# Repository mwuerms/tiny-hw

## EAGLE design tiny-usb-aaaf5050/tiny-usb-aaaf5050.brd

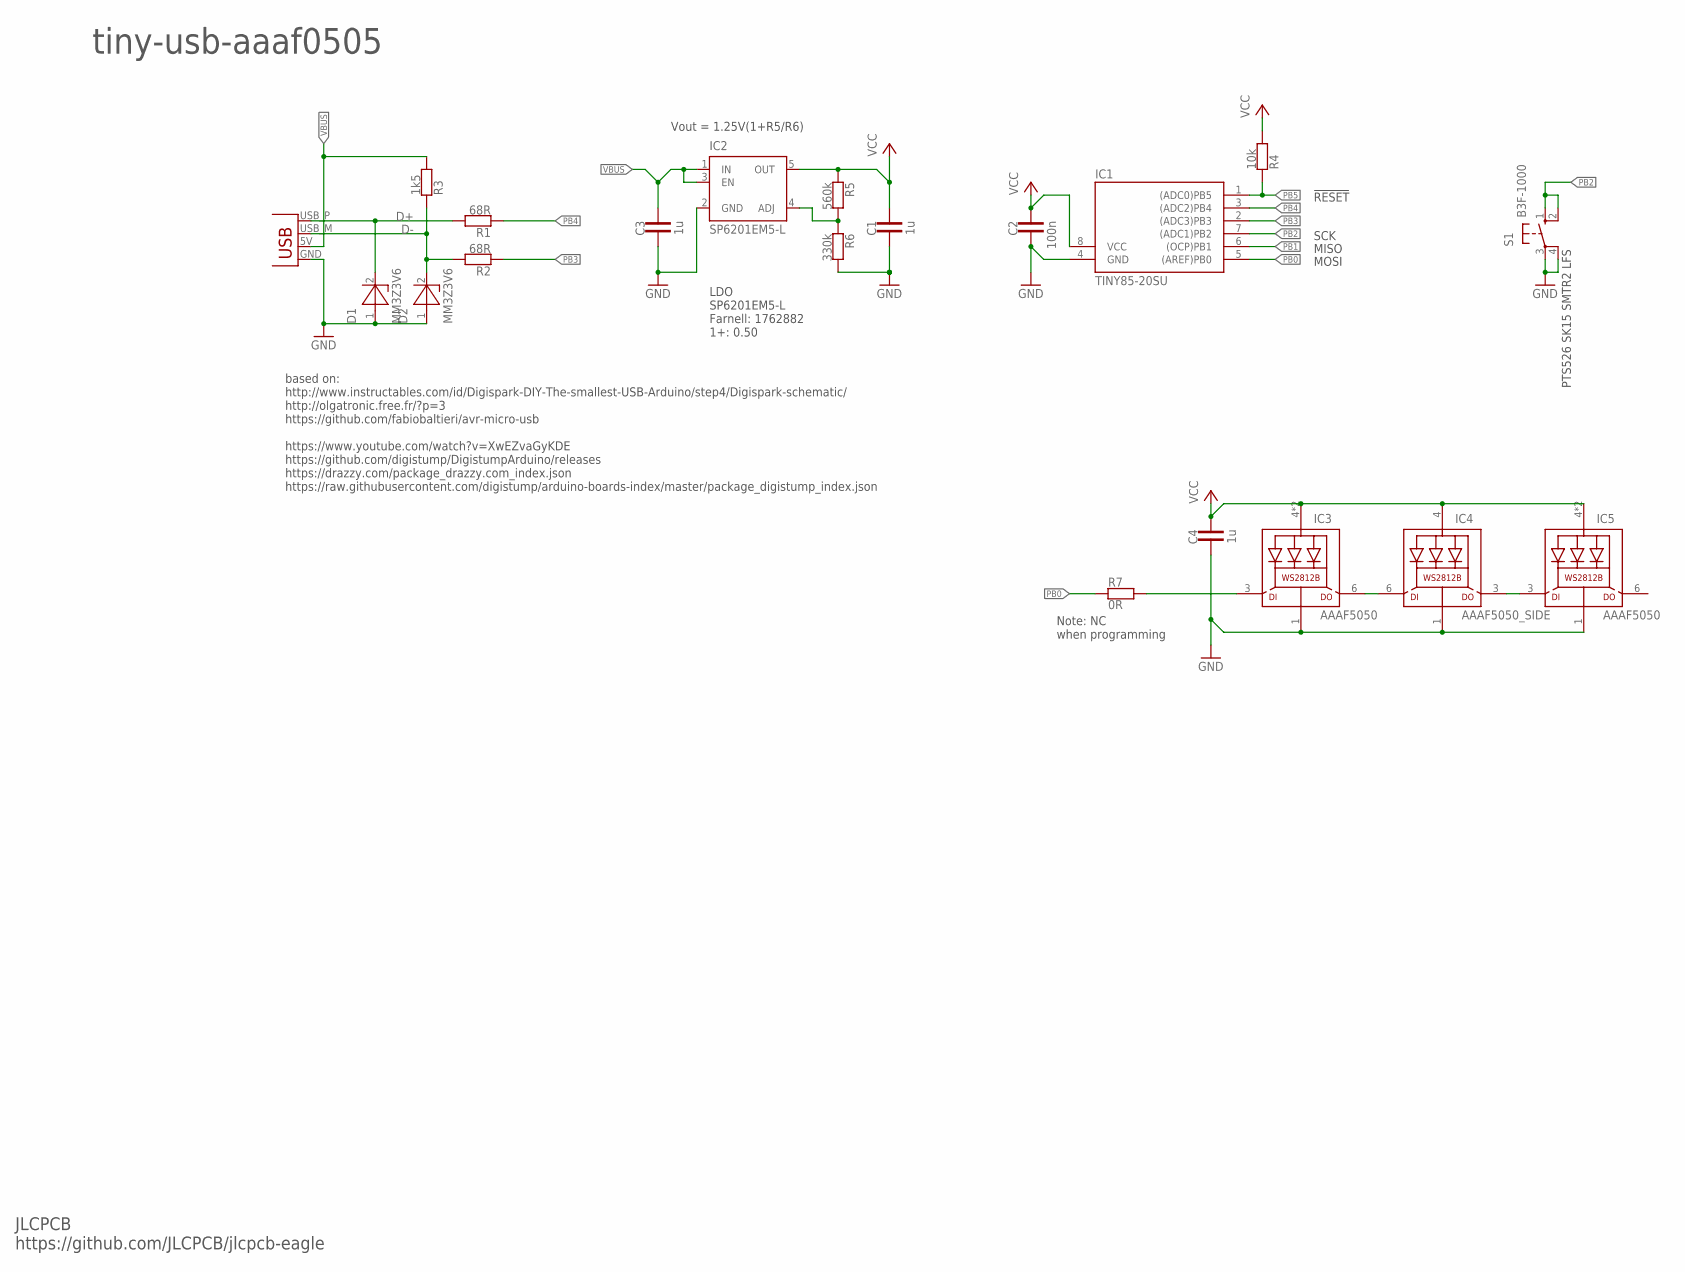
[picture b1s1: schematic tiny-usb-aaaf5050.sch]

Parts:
C1, C3: 1u; 0603MIL
C2: 100n; 0603MIL
C4: 1u; 0805MIL
D1, D2: MM3Z3V6; SOD-923F
IC1: TINY85-20SU; SOIC8
IC2: SP6201EM5-L; SOT23-5
IC3, IC5: AAAF5050
IC4: AAAF5050_SIDE
R1, R2: 68R; 0603MIL
R3: 1k5; 0603MIL
R4: 10k; 0603MIL
R5: 560k; 0603MIL
R6: 330k; 0603MIL
R7: 0R; 0603MIL
S1: B3F-1000; B3F-10SMD
X1: USBPCB; USB-A-PCB

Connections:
D+: D1.2 (K), R1.2, X1.USB_P (D+)
D-: D2.2 (K), R2.2, R3.1, X1.USB_M (D-)
DIN1: IC3.3 (DI), R7.2
DIN2: IC3.6 (DO), IC4.6 (DI)
DIN3: IC4.3 (DO), IC5.3 (DI)
GND: C1.2, C2.2, C3.2, C4.2, D1.1 (A), D2.1 (A), IC1.4 (GND), IC2.2 (GND), IC3.1 (GND), IC4.1 (GND), IC5.1 (GND), R6.2, S1.3, S1.4 (P1), X1.GND
unnamed: IC2.4 (ADJ), R5.2, R6.1
PB0: IC1.5 ((AREF)PB0), R7.1
PB1: IC1.6 ((OCP)PB1)
PB2: IC1.7 ((ADC1)PB2), S1.1 (S), S1.2 (S1)
PB3: IC1.2 ((ADC3)PB3), R2.1
PB4: IC1.3 ((ADC2)PB4), R1.1
PB5: IC1.1 ((ADC0)PB5), R4.1
VBUS: C3.1, IC2.1 (IN), IC2.3 (EN), R3.2, X1.5V (VBUS)
VCC: C1.1, C2.1, C4.1, IC1.8 (VCC), IC2.5 (OUT), IC3.4 (VDD), IC3.5 (VDD), IC4.4 (VDD), IC5.4 (VDD), IC5.5 (VDD), R4.2, R5.1

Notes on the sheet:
based on: http://www.instructables.com/id/Digispark-DIY-The-smallest-USB-Arduino/step4/Digispark-schematic/ http://olgatronic.free.fr/?p=3 https://github.com/fabiobaltieri/avr-micro-usb https://www.youtube.com/watch?v=XwEZvaGyKDE https://github.com/digistump/DigistumpArduino/releases https://drazzy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
LDO SP6201EM5-L Farnell: 1762882 1+: 0.50
Vout = 1.25V(1+R5/R6)
tiny-usb-aaaf0505
JLCPCB https://github.com/JLCPCB/jlcpcb-eagle
PTS526 SK15 SMTR2 LFS
!RESET!
MOSI
MISO
SCK
Note: NC when programming

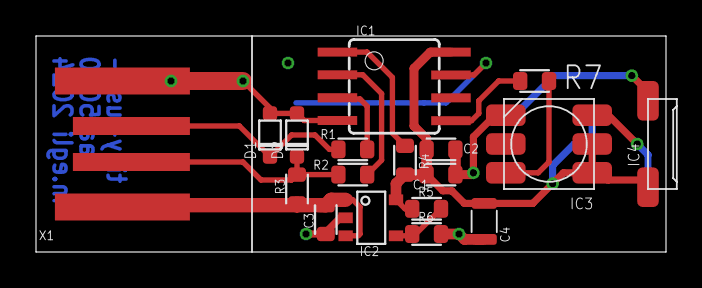
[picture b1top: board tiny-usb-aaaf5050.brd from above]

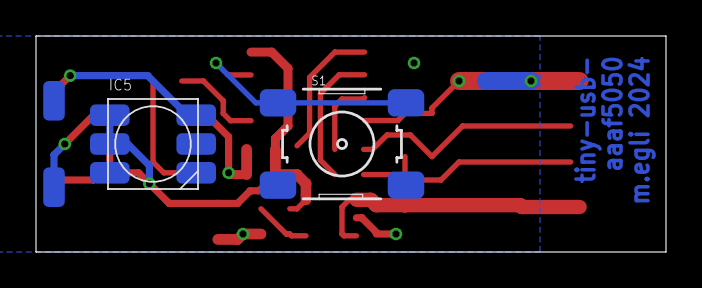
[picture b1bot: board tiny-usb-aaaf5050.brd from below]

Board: 2 copper layers, 35.0 x 12.0 mm, 20 parts (2 on the bottom side), 14 nets.

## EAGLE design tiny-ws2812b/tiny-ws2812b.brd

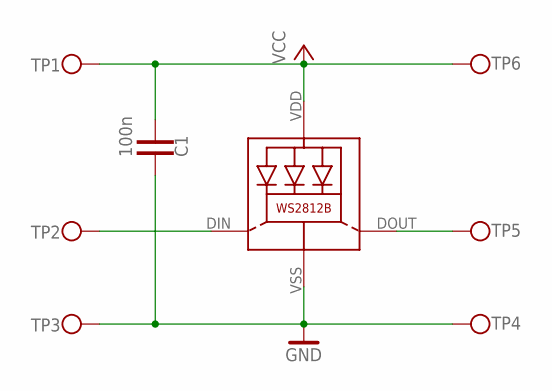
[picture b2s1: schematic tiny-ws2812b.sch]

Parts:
C1: 100n; 0603MIL
LED1: WS2812B
TP1, TP2, TP3, TP4, TP5, TP6: TP_Q2X1MM; PAD_Q2X1MM

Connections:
GND: C1.1, LED1.VSS (GND), TP3.1, TP4.1
unnamed: LED1.DOUT (DO), TP5.1
unnamed: LED1.DIN (DI), TP2.1
VCC: C1.2, LED1.VDD, TP1.1, TP6.1

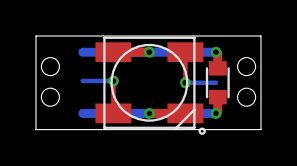
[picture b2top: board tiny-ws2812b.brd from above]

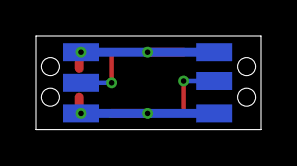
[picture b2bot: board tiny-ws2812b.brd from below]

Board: 2 copper layers, 12.5 x 5.2 mm, 8 parts (6 on the bottom side), 4 nets.

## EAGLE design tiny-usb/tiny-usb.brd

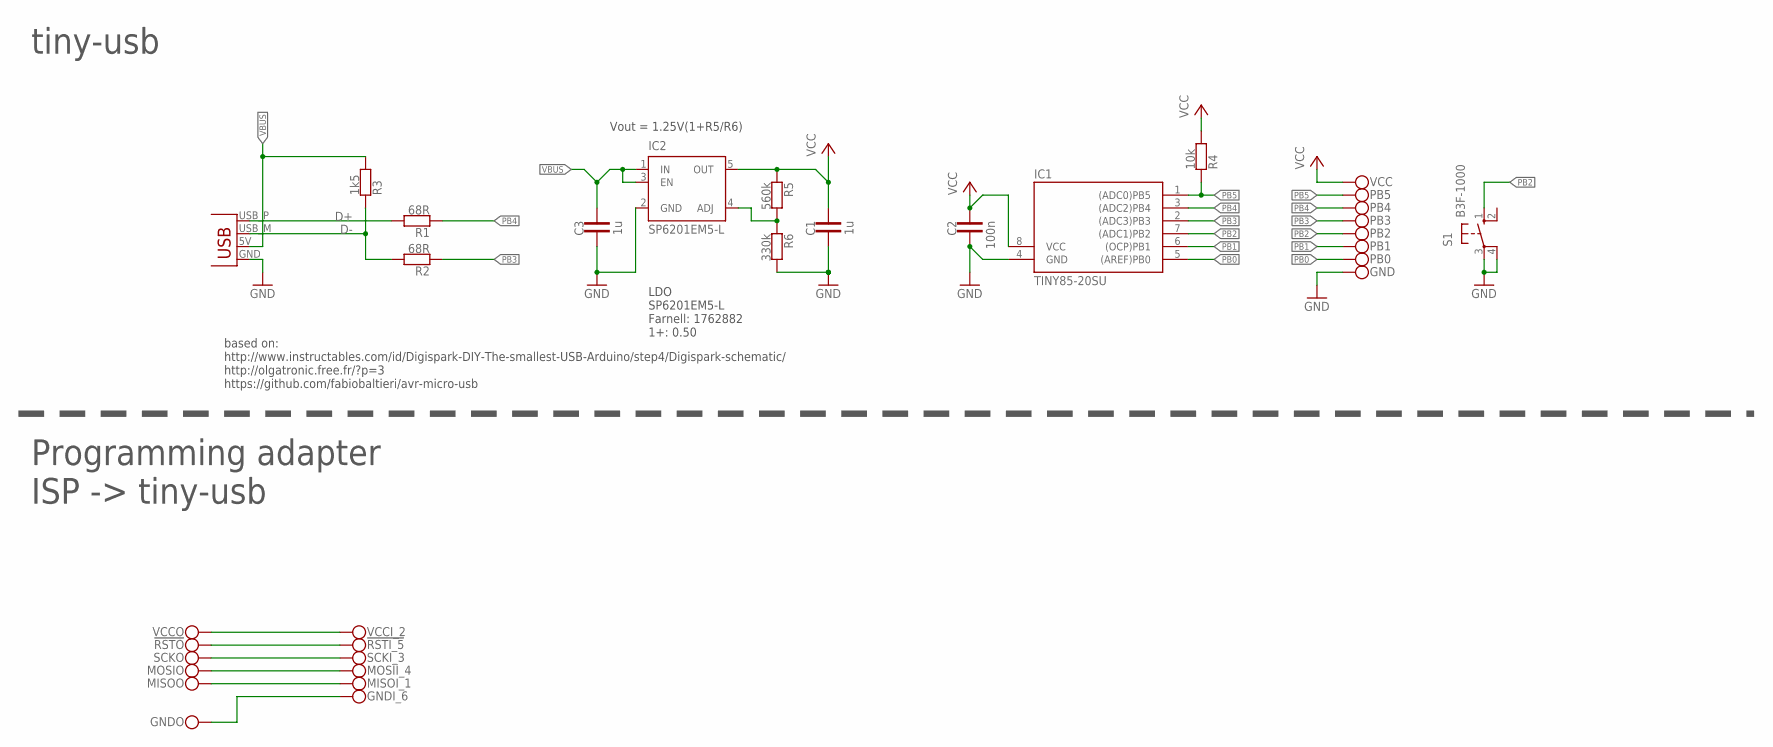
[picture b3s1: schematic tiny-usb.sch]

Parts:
!RSTI_5: TP_Q3X1.5MM; PAD_Q1.5X3MM
!RSTO: TP_Q3X1.5MM; PAD_Q1.5X3MM
C1, C3: 1u; 0603MIL
C2: 100n; 0603MIL
GND: TP_Q3X1.5MM; PAD_Q1.5X3MM
GNDI_6: TP_Q3X1.5MM; PAD_Q1.5X3MM
GNDO: TP_Q3X1.5MM; PAD_Q1.5X3MM
IC1: TINY85-20SU; SOIC8
IC2: SP6201EM5-L; SOT23-5
MISOI_1: TP_Q3X1.5MM; PAD_Q1.5X3MM
MISOO: TP_Q3X1.5MM; PAD_Q1.5X3MM
MOSII_4: TP_Q3X1.5MM; PAD_Q1.5X3MM
MOSIO: TP_Q3X1.5MM; PAD_Q1.5X3MM
PB0, PB1, PB2, PB3, PB4, PB5: TP_Q3X1.5MM; PAD_Q1.5X3MM
R1, R2: 68R; 0603MIL
R3: 1k5; 0603MIL
R4: 10k; 0603MIL
R5: 560k; 0603MIL
R6: 330k; 0603MIL
S1: B3F-1000; B3F-10SMD
SCKI_3: TP_Q3X1.5MM; PAD_Q1.5X3MM
SCKO: TP_Q3X1.5MM; PAD_Q1.5X3MM
VCC: TP_Q3X1.5MM; PAD_Q1.5X3MM
VCCI_2: TP_Q3X1.5MM; PAD_Q1.5X3MM
VCCO: TP_Q3X1.5MM; PAD_Q1.5X3MM
X1: USBPCB; USB-A-PCB

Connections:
!ISP_RST: !RSTI_5.1, !RSTO.1
D+: R1.2, X1.USB_P (D+)
D-: R2.2, R3.1, X1.USB_M (D-)
GND: C1.2, C2.2, C3.2, GND.1, IC1.4 (GND), IC2.2 (GND), R6.2, S1.3, S1.4 (P1), X1.GND
ISP_GND: GNDI_6.1, GNDO.1
ISP_MISO: MISOI_1.1, MISOO.1
ISP_MOSI: MOSII_4.1, MOSIO.1
ISP_SCK: SCKI_3.1, SCKO.1
ISP_VCC: VCCI_2.1, VCCO.1
unnamed: IC2.4 (ADJ), R5.2, R6.1
PB0: IC1.5 ((AREF)PB0), PB0.1
PB1: IC1.6 ((OCP)PB1), PB1.1
PB2: IC1.7 ((ADC1)PB2), PB2.1, S1.1 (S)
PB3: IC1.2 ((ADC3)PB3), PB3.1, R2.1
PB4: IC1.3 ((ADC2)PB4), PB4.1, R1.1
PB5: IC1.1 ((ADC0)PB5), PB5.1, R4.1
VBUS: C3.1, IC2.1 (IN), IC2.3 (EN), R3.2, X1.5V (VBUS)
VCC: C1.1, C2.1, IC1.8 (VCC), IC2.5 (OUT), R4.2, R5.1, VCC.1

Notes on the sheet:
based on: http://www.instructables.com/id/Digispark-DIY-The-smallest-USB-Arduino/step4/Digispark-schematic/ http://olgatronic.free.fr/?p=3 https://github.com/fabiobaltieri/avr-micro-usb
LDO SP6201EM5-L Farnell: 1762882 1+: 0.50
Vout = 1.25V(1+R5/R6)
tiny-usb
Programming adapter ISP -> tiny-usb

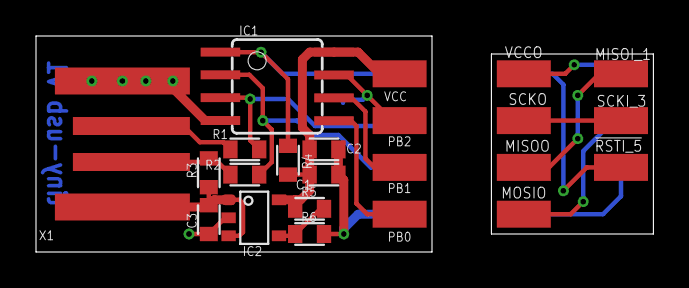
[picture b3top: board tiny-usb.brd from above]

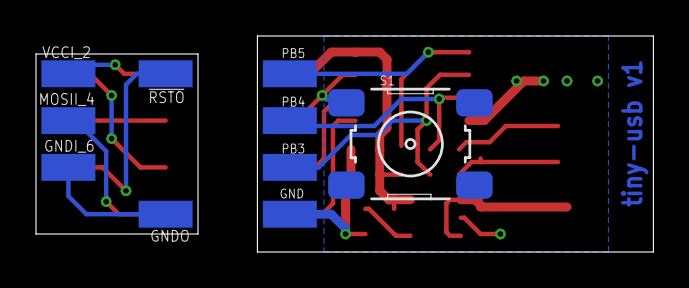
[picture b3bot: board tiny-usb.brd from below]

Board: 2 copper layers, 34.3 x 12.0 mm, 33 parts (10 on the bottom side), 18 nets.

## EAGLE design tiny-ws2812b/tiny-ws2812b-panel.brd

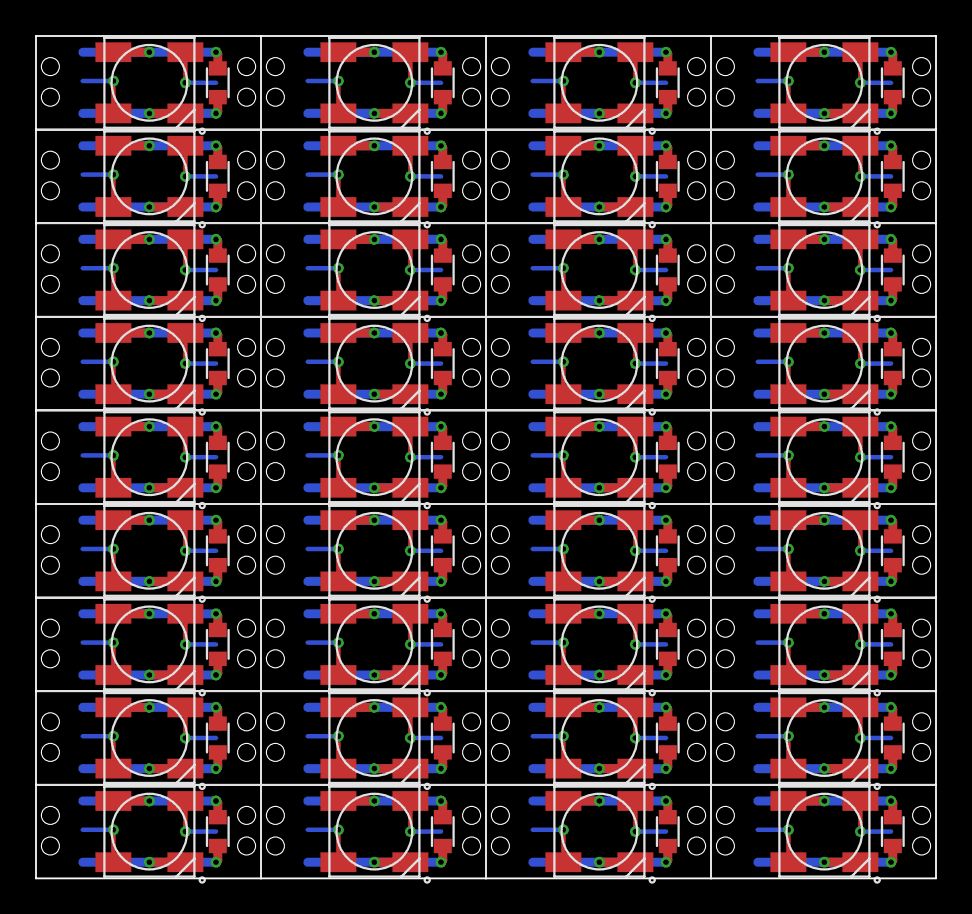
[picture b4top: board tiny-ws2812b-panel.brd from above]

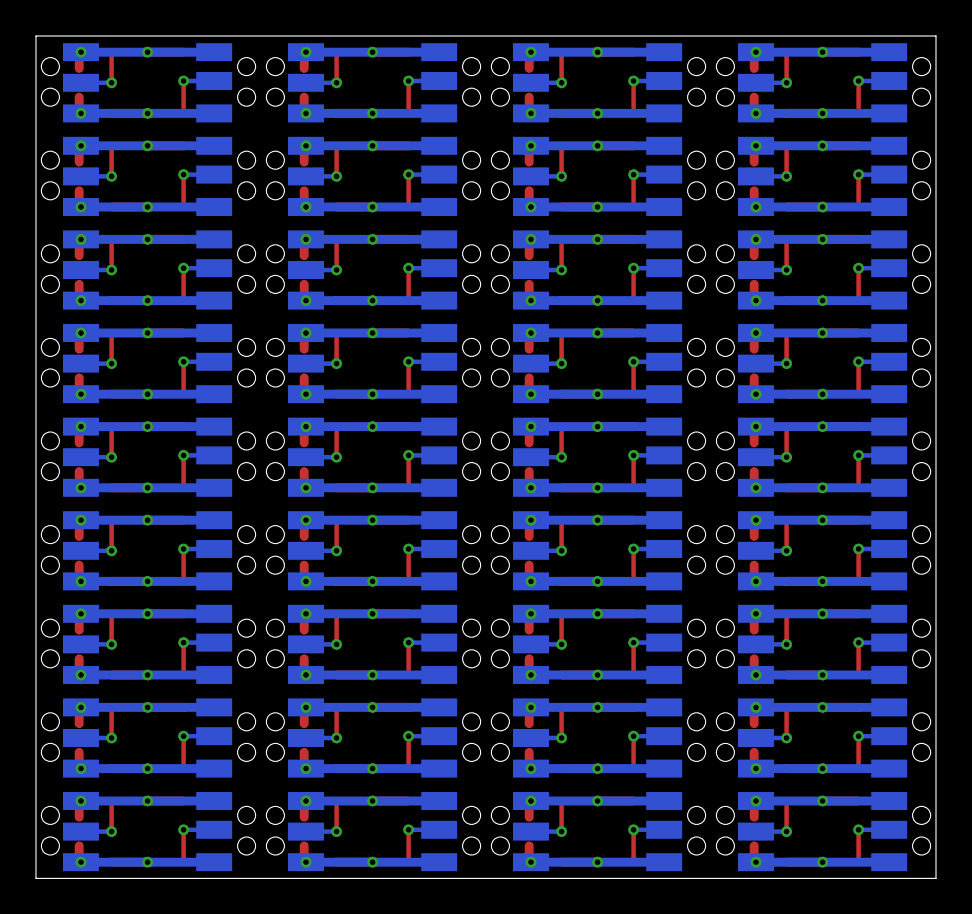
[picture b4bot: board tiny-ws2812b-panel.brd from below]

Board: 2 copper layers, 50.0 x 46.8 mm, 288 parts (216 on the bottom side), 144 nets.

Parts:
C1, C2, C3, C4, C5, C6, C7, C8, C9, C10, C11, C12, C13, C14, C15, C16, C17, C18, C19, C20, C21, C22, C23, C24, C25, C26, C27, C28, C29, C30, C31, C32, C33, C34, C35, C36: 100n; 0603MIL
LED1, LED2, LED3, LED4, LED5, LED6, LED7, LED8, LED9, LED10, LED11, LED12, LED13, LED14, LED15, LED16, LED17, LED18, LED19, LED20, LED21, LED22, LED23, LED24, LED25, LED26, LED27, LED28, LED29, LED30, LED31, LED32, LED33, LED34, LED35, LED36: WS2812B
TP1, TP2, TP3, TP4, TP5, TP6, TP7, TP8, TP9, TP10, TP11, TP12, TP13, TP14, TP15, TP16, TP17, TP18, TP19, TP20, TP21, TP22, TP23, TP24, TP25, TP26, TP27, TP28, TP29, TP30, TP31, TP32, TP33, TP34, TP35, TP36, TP37, TP38, TP39, TP40, TP41, TP42, TP43, TP44, TP45, TP46, TP47, TP48, TP49, TP50, TP51, TP52, TP53, TP54, TP55, TP56, TP57, TP58, TP59, TP60, TP61, TP62, TP63, TP64, TP65, TP66, TP67, TP68, TP69, TP70, TP71, TP72, TP73, TP74, TP75, TP76, TP77, TP78, TP79, TP80, TP81, TP82, TP83, TP84, TP85, TP86, TP87, TP88, TP89, TP90, TP91, TP92, TP93, TP94, TP95, TP96, TP97, TP98, TP99, TP100, TP101, TP102, TP103, TP104, TP105, TP106, TP107, TP108, TP109, TP110, TP111, TP112, TP113, TP114, TP115, TP116, TP117, TP118, TP119, TP120, TP121, TP122, TP123, TP124, TP125, TP126, TP127, TP128, TP129, TP130, TP131, TP132, TP133, TP134, TP135, TP136, TP137, TP138, TP139, TP140, TP141, TP142, TP143, TP144, TP145, TP146, TP147, TP148, TP149, TP150, TP151, TP152, TP153, TP154, TP155, TP156, TP157, TP158, TP159, TP160, TP161, TP162, TP163, TP164, TP165, TP166, TP167, TP168, TP169, TP170, TP171, TP172, TP173, TP174, TP175, TP176, TP177, TP178, TP179, TP180, TP181, TP182, TP183, TP184, TP185, TP186, TP187, TP188, TP189, TP190, TP191, TP192, TP193, TP194, TP195, TP196, TP197, TP198, TP199, TP200, TP201, TP202, TP203, TP204, TP205, TP206, TP207, TP208, TP209, TP210, TP211, TP212, TP213, TP214, TP215, TP216: TP_Q2X1MM; PAD_Q2X1MM

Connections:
GND: C1.1, LED1.VSS, TP3.1, TP4.1
GND1: C2.1, LED2.VSS, TP9.1, TP10.1
GND2: C3.1, LED3.VSS, TP15.1, TP16.1
GND3: C4.1, LED4.VSS, TP21.1, TP22.1
GND4: C5.1, LED5.VSS, TP27.1, TP28.1
GND5: C6.1, LED6.VSS, TP33.1, TP34.1
GND6: C7.1, LED7.VSS, TP39.1, TP40.1
GND7: C8.1, LED8.VSS, TP45.1, TP46.1
GND8: C9.1, LED9.VSS, TP51.1, TP52.1
GND9: C10.1, LED10.VSS, TP57.1, TP58.1
GND10: C11.1, LED11.VSS, TP63.1, TP64.1
GND11: C12.1, LED12.VSS, TP69.1, TP70.1
GND12: C13.1, LED13.VSS, TP75.1, TP76.1
GND13: C14.1, LED14.VSS, TP81.1, TP82.1
GND14: C15.1, LED15.VSS, TP87.1, TP88.1
GND15: C16.1, LED16.VSS, TP93.1, TP94.1
GND16: C17.1, LED17.VSS, TP99.1, TP100.1
GND17: C18.1, LED18.VSS, TP105.1, TP106.1
GND18: C19.1, LED19.VSS, TP111.1, TP112.1
GND19: C20.1, LED20.VSS, TP117.1, TP118.1
GND20: C21.1, LED21.VSS, TP123.1, TP124.1
GND21: C22.1, LED22.VSS, TP129.1, TP130.1
GND22: C23.1, LED23.VSS, TP135.1, TP136.1
GND23: C24.1, LED24.VSS, TP141.1, TP142.1
GND24: C25.1, LED25.VSS, TP147.1, TP148.1
GND25: C26.1, LED26.VSS, TP153.1, TP154.1
GND26: C27.1, LED27.VSS, TP159.1, TP160.1
GND27: C28.1, LED28.VSS, TP165.1, TP166.1
GND28: C29.1, LED29.VSS, TP171.1, TP172.1
GND29: C30.1, LED30.VSS, TP177.1, TP178.1
GND30: C31.1, LED31.VSS, TP183.1, TP184.1
GND31: C32.1, LED32.VSS, TP189.1, TP190.1
GND32: C33.1, LED33.VSS, TP195.1, TP196.1
GND33: C34.1, LED34.VSS, TP201.1, TP202.1
GND34: C35.1, LED35.VSS, TP207.1, TP208.1
GND35: C36.1, LED36.VSS, TP213.1, TP214.1
unnamed: LED1.DOUT, TP5.1
unnamed: LED1.DIN, TP2.1
unnamed: LED2.DOUT, TP11.1
unnamed: LED2.DIN, TP8.1
unnamed: LED3.DOUT, TP17.1
unnamed: LED3.DIN, TP14.1
unnamed: LED4.DOUT, TP23.1
unnamed: LED4.DIN, TP20.1
unnamed: LED5.DOUT, TP29.1
unnamed: LED5.DIN, TP26.1
unnamed: LED6.DOUT, TP35.1
unnamed: LED6.DIN, TP32.1
unnamed: LED7.DOUT, TP41.1
unnamed: LED7.DIN, TP38.1
unnamed: LED8.DOUT, TP47.1
unnamed: LED8.DIN, TP44.1
unnamed: LED9.DOUT, TP53.1
unnamed: LED9.DIN, TP50.1
unnamed: LED10.DOUT, TP59.1
unnamed: LED10.DIN, TP56.1
unnamed: LED11.DOUT, TP65.1
unnamed: LED11.DIN, TP62.1
unnamed: LED12.DOUT, TP71.1
unnamed: LED12.DIN, TP68.1
unnamed: LED13.DOUT, TP77.1
unnamed: LED13.DIN, TP74.1
unnamed: LED14.DOUT, TP83.1
unnamed: LED14.DIN, TP80.1
unnamed: LED15.DOUT, TP89.1
unnamed: LED15.DIN, TP86.1
unnamed: LED16.DOUT, TP95.1
unnamed: LED16.DIN, TP92.1
unnamed: LED17.DOUT, TP101.1
unnamed: LED17.DIN, TP98.1
unnamed: LED18.DOUT, TP107.1
unnamed: LED18.DIN, TP104.1
unnamed: LED19.DOUT, TP113.1
unnamed: LED19.DIN, TP110.1
unnamed: LED20.DOUT, TP119.1
unnamed: LED20.DIN, TP116.1
unnamed: LED21.DOUT, TP125.1
unnamed: LED21.DIN, TP122.1
unnamed: LED22.DOUT, TP131.1
unnamed: LED22.DIN, TP128.1
unnamed: LED23.DOUT, TP137.1
unnamed: LED23.DIN, TP134.1
unnamed: LED24.DOUT, TP143.1
unnamed: LED24.DIN, TP140.1
unnamed: LED25.DOUT, TP149.1
unnamed: LED25.DIN, TP146.1
unnamed: LED26.DOUT, TP155.1
unnamed: LED26.DIN, TP152.1
unnamed: LED27.DOUT, TP161.1
unnamed: LED27.DIN, TP158.1
unnamed: LED28.DOUT, TP167.1
unnamed: LED28.DIN, TP164.1
unnamed: LED29.DOUT, TP173.1
unnamed: LED29.DIN, TP170.1
unnamed: LED30.DOUT, TP179.1
unnamed: LED30.DIN, TP176.1
unnamed: LED31.DOUT, TP185.1
unnamed: LED31.DIN, TP182.1
unnamed: LED32.DOUT, TP191.1
unnamed: LED32.DIN, TP188.1
unnamed: LED33.DOUT, TP197.1
unnamed: LED33.DIN, TP194.1
unnamed: LED34.DOUT, TP203.1
unnamed: LED34.DIN, TP200.1
unnamed: LED35.DOUT, TP209.1
unnamed: LED35.DIN, TP206.1
unnamed: LED36.DOUT, TP215.1
unnamed: LED36.DIN, TP212.1
VCC: C1.2, LED1.VDD, TP1.1, TP6.1
VCC1: C2.2, LED2.VDD, TP7.1, TP12.1
VCC2: C3.2, LED3.VDD, TP13.1, TP18.1
VCC3: C4.2, LED4.VDD, TP19.1, TP24.1
VCC4: C5.2, LED5.VDD, TP25.1, TP30.1
VCC5: C6.2, LED6.VDD, TP31.1, TP36.1
VCC6: C7.2, LED7.VDD, TP37.1, TP42.1
VCC7: C8.2, LED8.VDD, TP43.1, TP48.1
VCC8: C9.2, LED9.VDD, TP49.1, TP54.1
VCC9: C10.2, LED10.VDD, TP55.1, TP60.1
VCC10: C11.2, LED11.VDD, TP61.1, TP66.1
VCC11: C12.2, LED12.VDD, TP67.1, TP72.1
VCC12: C13.2, LED13.VDD, TP73.1, TP78.1
VCC13: C14.2, LED14.VDD, TP79.1, TP84.1
VCC14: C15.2, LED15.VDD, TP85.1, TP90.1
VCC15: C16.2, LED16.VDD, TP91.1, TP96.1
VCC16: C17.2, LED17.VDD, TP97.1, TP102.1
VCC17: C18.2, LED18.VDD, TP103.1, TP108.1
VCC18: C19.2, LED19.VDD, TP109.1, TP114.1
VCC19: C20.2, LED20.VDD, TP115.1, TP120.1
VCC20: C21.2, LED21.VDD, TP121.1, TP126.1
VCC21: C22.2, LED22.VDD, TP127.1, TP132.1
VCC22: C23.2, LED23.VDD, TP133.1, TP138.1
VCC23: C24.2, LED24.VDD, TP139.1, TP144.1
VCC24: C25.2, LED25.VDD, TP145.1, TP150.1
VCC25: C26.2, LED26.VDD, TP151.1, TP156.1
VCC26: C27.2, LED27.VDD, TP157.1, TP162.1
VCC27: C28.2, LED28.VDD, TP163.1, TP168.1
VCC28: C29.2, LED29.VDD, TP169.1, TP174.1
VCC29: C30.2, LED30.VDD, TP175.1, TP180.1
VCC30: C31.2, LED31.VDD, TP181.1, TP186.1
VCC31: C32.2, LED32.VDD, TP187.1, TP192.1
VCC32: C33.2, LED33.VDD, TP193.1, TP198.1
VCC33: C34.2, LED34.VDD, TP199.1, TP204.1
VCC34: C35.2, LED35.VDD, TP205.1, TP210.1
VCC35: C36.2, LED36.VDD, TP211.1, TP216.1

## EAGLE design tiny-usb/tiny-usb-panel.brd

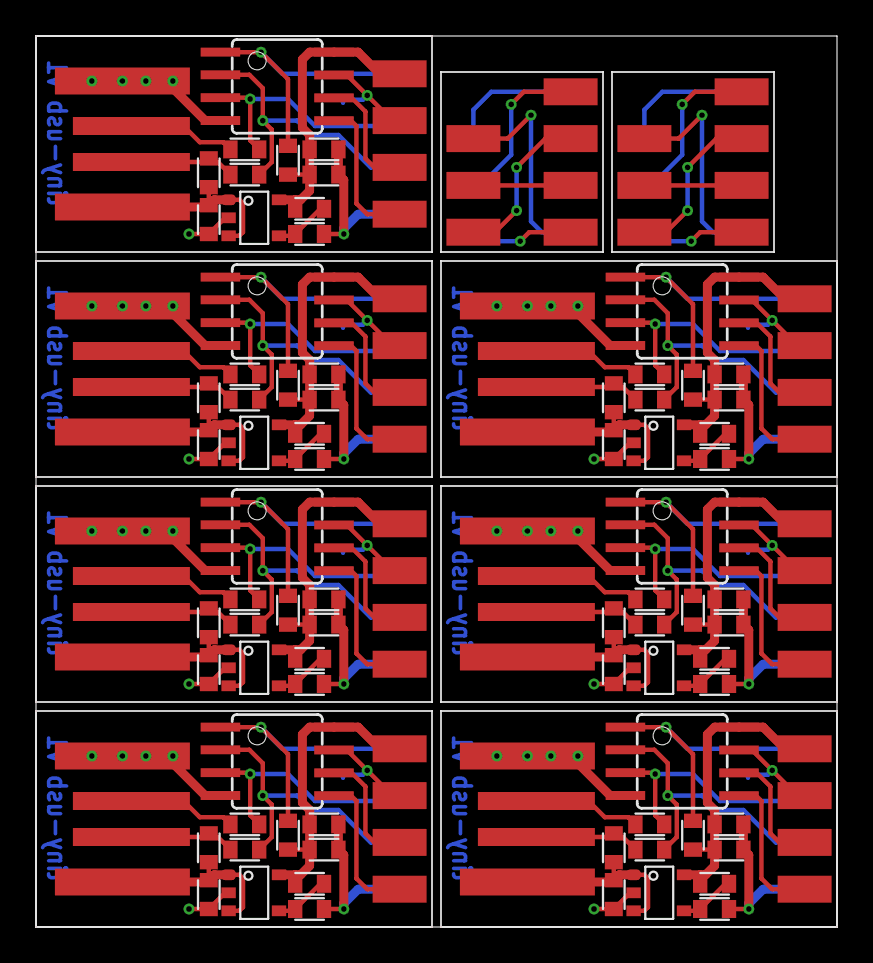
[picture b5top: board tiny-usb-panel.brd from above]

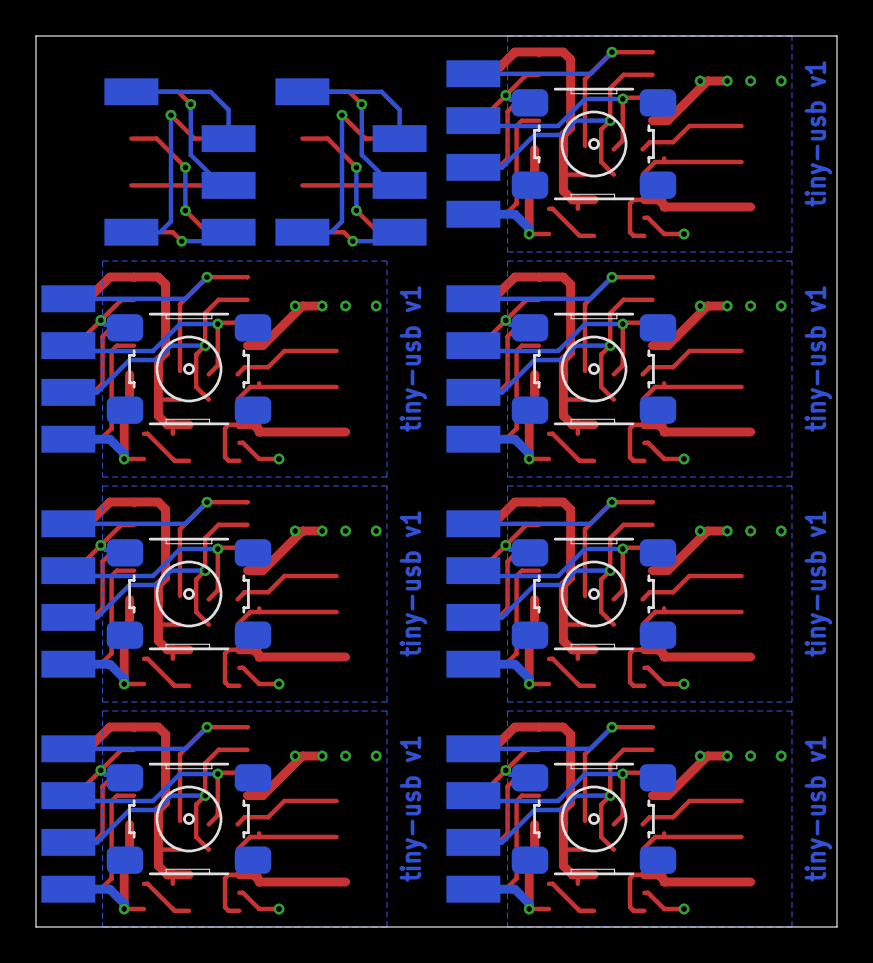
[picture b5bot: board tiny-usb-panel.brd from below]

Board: 2 copper layers, 44.5 x 49.5 mm, 171 parts (45 on the bottom side), 96 nets.

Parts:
!RSTI_1, !RSTI_5: TP_Q3X1.5MM; PAD_Q1.5X3MM
!RSTO, !RSTO1: TP_Q3X1.5MM; PAD_Q1.5X3MM
C1, C3, C4, C6, C7, C9, C10, C12, C13, C15, C16, C18, C19, C21: 1u; 0603MIL
C2, C5, C8, C11, C14, C17, C20: 100n; 0603MIL
GND, GND1, GND2, GND3, GND4, GND5, GND6: TP_Q3X1.5MM; PAD_Q1.5X3MM
GNDI_1, GNDI_6: TP_Q3X1.5MM; PAD_Q1.5X3MM
GNDO, GNDO1: TP_Q3X1.5MM; PAD_Q1.5X3MM
IC1, IC3, IC5, IC7, IC9, IC11, IC13: TINY85-20SU; SOIC8
IC2, IC4, IC6, IC8, IC10, IC12, IC14: SP6201EM5-L; SOT23-5
MISOI_1, MISOI_2: TP_Q3X1.5MM; PAD_Q1.5X3MM
MISOO, MISOO1: TP_Q3X1.5MM; PAD_Q1.5X3MM
MOSII_1, MOSII_4: TP_Q3X1.5MM; PAD_Q1.5X3MM
MOSIO, MOSIO1: TP_Q3X1.5MM; PAD_Q1.5X3MM
PB0, PB1, PB2, PB3, PB4, PB5, PB6, PB7, PB8, PB9, PB10, PB11, PB12, PB13, PB14, PB15, PB16, PB17, PB18, PB19, PB20, PB21, PB22, PB23, PB24, PB25, PB26, PB27, PB28, PB29, PB30, PB31, PB32, PB33, PB34, PB35, PB36, PB37, PB38, PB39, PB40, PB41: TP_Q3X1.5MM; PAD_Q1.5X3MM
R1, R2, R5, R6, R7, R9, R11, R12, R13, R15, R17, R18, R19, R21, R23, R24, R25, R27, R29, R30, R31, R33, R35, R36, R37, R39, R41, R42: 68R; 0603MIL
R3, R8, R14, R20, R26, R32, R38: 1k5; 0603MIL
R4, R10, R16, R22, R28, R34, R40: 10k; 0603MIL
S1, S2, S3, S4, S5, S6, S7: B3F-1000; B3F-10SMD
SCKI_1, SCKI_3: TP_Q3X1.5MM; PAD_Q1.5X3MM
SCKO, SCKO1: TP_Q3X1.5MM; PAD_Q1.5X3MM
VCC, VCC1, VCC2, VCC3, VCC4, VCC5, VCC6: TP_Q3X1.5MM; PAD_Q1.5X3MM
VCCI_1, VCCI_2: TP_Q3X1.5MM; PAD_Q1.5X3MM
VCCO, VCCO1: TP_Q3X1.5MM; PAD_Q1.5X3MM
X1, X2, X3, X4, X5, X6, X7: USBPCB; USB-A-PCB

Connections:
!ISP_RST: !RSTI_5.1, !RSTO.1
!ISP_RST1: !RSTI_1.1, !RSTO1.1
D+: R1.2, X1.USB_P
D+1: R7.2, X2.USB_P
D+2: R13.2, X3.USB_P
D+3: R19.2, X4.USB_P
D+4: R25.2, X5.USB_P
D+5: R31.2, X6.USB_P
D+6: R37.2, X7.USB_P
D-: R2.2, R3.1, X1.USB_M
D-1: R8.1, R9.2, X2.USB_M
D-2: R14.1, R15.2, X3.USB_M
D-3: R20.1, R21.2, X4.USB_M
D-4: R26.1, R27.2, X5.USB_M
D-5: R32.1, R33.2, X6.USB_M
D-6: R38.1, R39.2, X7.USB_M
GND: C1.2, C2.2, C3.2, GND.1, IC1.4, IC2.2, R6.2, S1.3, S1.4, X1.GND
GND1: C4.2, C5.2, C6.2, GND1.1, IC3.4, IC4.2, R12.2, S2.3, S2.4, X2.GND
GND2: C7.2, C8.2, C9.2, GND2.1, IC5.4, IC6.2, R18.2, S3.3, S3.4, X3.GND
GND3: C10.2, C11.2, C12.2, GND3.1, IC7.4, IC8.2, R24.2, S4.3, S4.4, X4.GND
GND8: C13.2, C14.2, C15.2, GND4.1, IC9.4, IC10.2, R30.2, S5.3, S5.4, X5.GND
GND9: C16.2, C17.2, C18.2, GND5.1, IC11.4, IC12.2, R36.2, S6.3, S6.4, X6.GND
GND10: C19.2, C20.2, C21.2, GND6.1, IC13.4, IC14.2, R42.2, S7.3, S7.4, X7.GND
ISP_GND: GNDI_6.1, GNDO.1
ISP_GND1: GNDI_1.1, GNDO1.1
ISP_MISO: MISOI_1.1, MISOO.1
ISP_MISO1: MISOI_2.1, MISOO1.1
ISP_MOSI: MOSII_4.1, MOSIO.1
ISP_MOSI1: MOSII_1.1, MOSIO1.1
ISP_SCK: SCKI_3.1, SCKO.1
ISP_SCK1: SCKI_1.1, SCKO1.1
ISP_VCC: VCCI_2.1, VCCO.1
ISP_VCC1: VCCI_1.1, VCCO1.1
unnamed: IC2.4, R5.2, R6.1
unnamed: IC4.4, R11.2, R12.1
unnamed: IC6.4, R17.2, R18.1
unnamed: IC8.4, R23.2, R24.1
unnamed: IC10.4, R29.2, R30.1
unnamed: IC12.4, R35.2, R36.1
unnamed: IC14.4, R41.2, R42.1
PB0: IC1.5, PB0.1
PB1: IC1.6, PB1.1
PB2: IC1.7, PB2.1, S1.1
PB3: IC1.2, PB3.1, R2.1
PB4: IC1.3, PB4.1, R1.1
PB5: IC1.1, PB5.1, R4.1
PB6: IC3.6, PB10.1
PB7: IC3.7, PB9.1, S2.1
PB8: IC3.5, PB11.1
PB9: IC3.2, PB8.1, R9.1
PB10: IC3.3, PB7.1, R7.1
PB11: IC3.1, PB6.1, R10.1
PB12: IC5.6, PB16.1
PB13: IC5.7, PB15.1, S3.1
PB14: IC5.5, PB17.1
PB15: IC5.2, PB14.1, R15.1
PB16: IC5.3, PB13.1, R13.1
PB17: IC5.1, PB12.1, R16.1
PB18: IC7.6, PB22.1
PB19: IC7.7, PB21.1, S4.1
PB20: IC7.5, PB23.1
PB21: IC7.2, PB20.1, R21.1
PB22: IC7.3, PB19.1, R19.1
PB23: IC7.1, PB18.1, R22.1
PB24: IC9.6, PB28.1
PB25: IC9.7, PB27.1, S5.1
PB26: IC9.5, PB29.1
PB27: IC9.2, PB26.1, R27.1
PB28: IC9.3, PB25.1, R25.1
PB29: IC9.1, PB24.1, R28.1
PB30: IC11.6, PB34.1
PB31: IC11.7, PB33.1, S6.1
PB32: IC11.5, PB35.1
PB33: IC11.2, PB32.1, R33.1
PB34: IC11.3, PB31.1, R31.1
PB35: IC11.1, PB30.1, R34.1
PB36: IC13.6, PB40.1
PB37: IC13.7, PB39.1, S7.1
PB38: IC13.5, PB41.1
PB39: IC13.2, PB38.1, R39.1
PB40: IC13.3, PB37.1, R37.1
PB41: IC13.1, PB36.1, R40.1
VBUS: C3.1, IC2.1, IC2.3, R3.2, X1.5V
VBUS1: C6.1, IC4.1, IC4.3, R8.2, X2.5V
VBUS2: C9.1, IC6.1, IC6.3, R14.2, X3.5V
VBUS3: C12.1, IC8.1, IC8.3, R20.2, X4.5V
VBUS4: C15.1, IC10.1, IC10.3, R26.2, X5.5V
VBUS5: C18.1, IC12.1, IC12.3, R32.2, X6.5V
VBUS6: C21.1, IC14.1, IC14.3, R38.2, X7.5V
VCC: C1.1, C2.1, IC1.8, IC2.5, R4.2, R5.1, VCC.1
VCC1: C4.1, C5.1, IC3.8, IC4.5, R10.2, R11.1, VCC1.1
VCC2: C7.1, C8.1, IC5.8, IC6.5, R16.2, R17.1, VCC2.1
VCC3: C10.1, C11.1, IC7.8, IC8.5, R22.2, R23.1, VCC3.1
VCC4: C13.1, C14.1, IC9.8, IC10.5, R28.2, R29.1, VCC4.1
VCC5: C16.1, C17.1, IC11.8, IC12.5, R34.2, R35.1, VCC5.1
VCC6: C19.1, C20.1, IC13.8, IC14.5, R40.2, R41.1, VCC6.1

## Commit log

2015-11-05 added projects tiny-usb + tiny-ws2812b
2024-01-24 tiny-usb-aaaf5050 created a small usb stick using attiny85 and 3 x AAAF5050 (neopixel like LEDs)
2024-01-24 tini-usb-aaaf5050 bei jlcpcb bestellt
2024-01-27 case: v1.0 added
2024-01-29 redesigned the case: v1.1
